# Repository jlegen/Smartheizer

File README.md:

# Smartheizer
## basic heating control

 I wanted some more control for my ancient heating system:
 * enable heating remotely before returning from holidays in winter :-)
 * record activity of heating system and hot water preparation
 * embed into my <a href="https://iobroker.net"> iobroker</a> system

 ##  The hardware in short:

* provides 3 isolated inputs for recording operation times (oil burner, pumps, hot water preparation)
* 3 relays to control heating operations, night setback remotely
* 3 plugs for DS18B20 temperature sensors
* socket for Wemos D1 Mini (or Pro)
* runs with <a href="https://tasmota.github.io/docs/"> Tasmota</a>

## Software needed
* Tasmota for the Wemos D1 on the PCB, which handles the GPIO inputs, Relays and temperature sensors
* a MQTT broker running somewhere, or a smart home software like iobroker or home assistant with MQTT enabled

## Tasmota config

Wemos D1 configuration in Tasmota:

Some Tasmota configurations can be easily applied using the web console. 

1) The GPIO polarity needs to be fixed:
<pre>
Backlog Switchmode1 2; Switchmode2 2; Switchmode3 2
</pre>

2) You also need to decouple the "Switches" (which are the GPIO inputs) from the Relays (it seems like a sort of 'tradition' with tasmota, that per default "Switch1" always triggers "Relay1" etc.).
<pre>
Rule1 on Switch1#state do Publish tele/tasmota_6E171C/SENSOR {"Time":"%timestamp%", "Burner":"%value%"} endon on Switch2#state do Publish tele/tasmota_6E171C/SENSOR {"Time":"%timestamp%", "Pump1":"%value%"} endon on Switch3#state do Publish tele/tasmota_6E171C/SENSOR {"Time":"%timestamp%", "Pump2":"%value%"} endon

Rule1 1
</pre>

Of course, you may chose different topics for MQTT. 
Btw, you don't even need to use these topics with your iobroker or other software - defining the "Rule1" alone enables Tasmota to send the switch states with MQTT as well.

New PCB revision

It works! :-)

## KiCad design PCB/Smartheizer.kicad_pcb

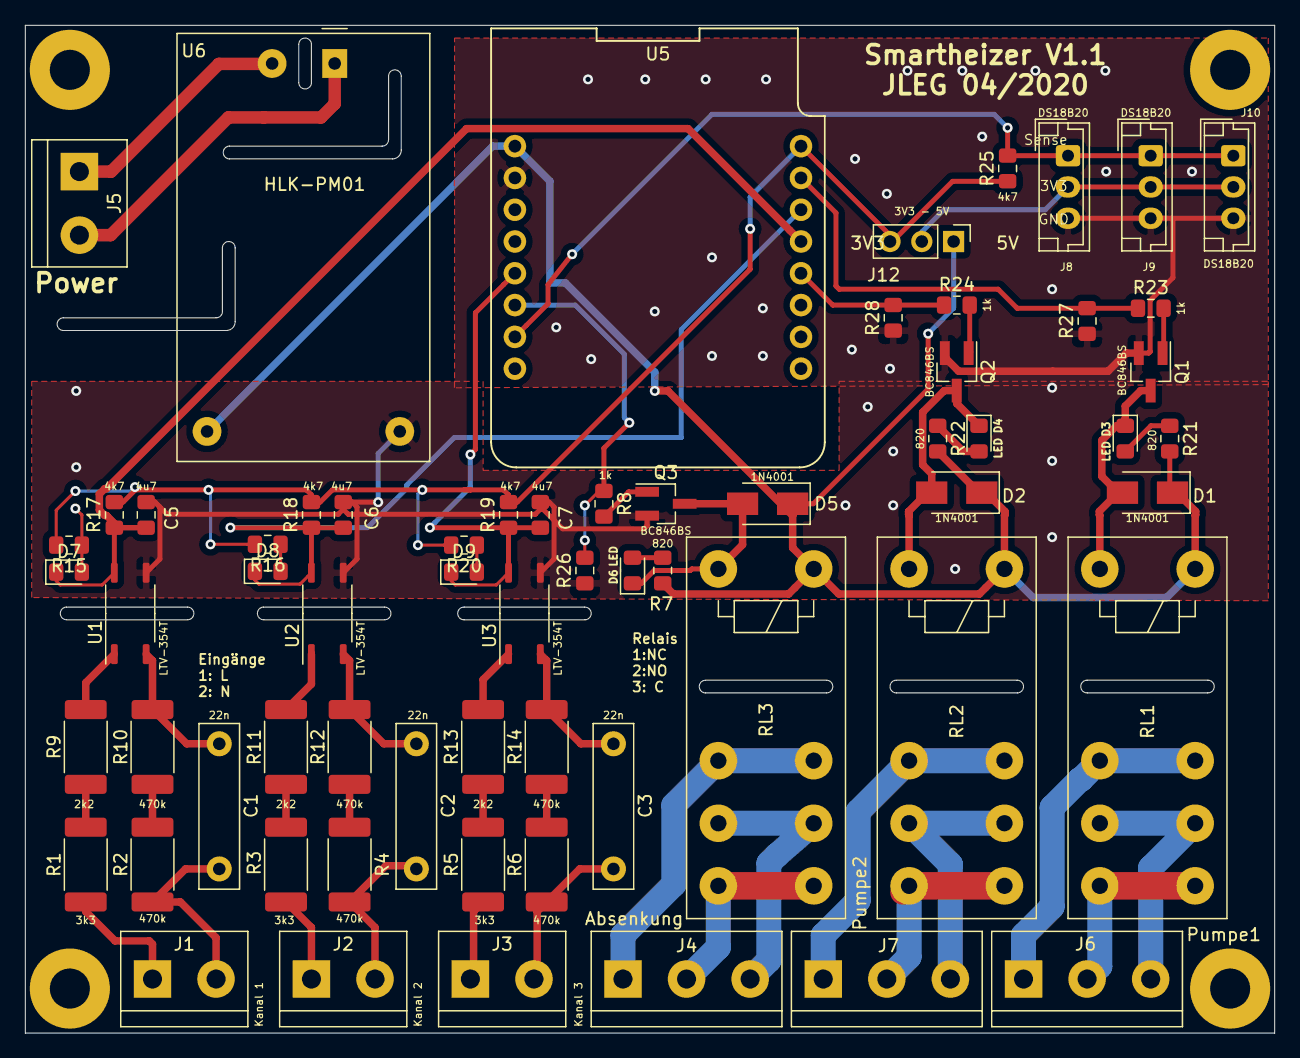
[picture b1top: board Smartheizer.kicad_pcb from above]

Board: 2 copper layers, 99.8 x 80.5 mm, 69 parts (0 on the bottom side), 52 nets.

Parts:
C1, C2, C3: 22n; C_Rect_L13.0mm_W3.0mm_P10.00mm_FKS3_FKP3_MKS4
C5, C6, C7: 4u7; C_0805_2012Metric_Pad1.15x1.40mm_HandSolder
D1, D2, D5: 1N4001; D_SMA
D3, D4, D6, D7, D8, D9: LED; LED_0805_2012Metric_Pad1.15x1.40mm_HandSolder
H1, H2, H3, H4: MountingHole; MountingHole_3.2mm_M3_Pad
J1, J2, J3, J5: Screw_Terminal_01x02; TerminalBlock_bornier-2_P5.08mm
J4: Absenkung; TerminalBlock_bornier-3_P5.08mm
J6: Pumpe1; TerminalBlock_bornier-3_P5.08mm
J7: Pumpe2; TerminalBlock_bornier-3_P5.08mm
J8, J9, J10: DS18B20; JST_EH_B03B-EH-A_1x03_P2.50mm_Vertical
J12: 3V3 - 5V; PinHeader_1x03_P2.54mm_Vertical
Q1, Q2, Q3: BC846BS; SOT-23_Handsoldering
R1, R3, R5: 3k3; R_2512_6332Metric_Pad1.52x3.35mm_HandSolder
R2, R4, R6, R10, R12, R14: 470k; R_2512_6332Metric_Pad1.52x3.35mm_HandSolder
R7, R21, R22: 820; R_0805_2012Metric_Pad1.15x1.40mm_HandSolder
R8, R15, R16, R20, R23, R24: 1k; R_0805_2012Metric_Pad1.15x1.40mm_HandSolder
R9, R11, R13: 2k2; R_2512_6332Metric_Pad1.52x3.35mm_HandSolder
R17, R18, R19, R25: 4k7; R_0805_2012Metric_Pad1.15x1.40mm_HandSolder
R26, R27, R28: 10k; R_0805_2012Metric_Pad1.15x1.40mm_HandSolder
RL1, RL2, RL3: G5Q-1; Relay_SPDT_Schrack-RP-II-1-16A-FormC_RM5mm
U1, U2, U3: LTV-354T; SOIC-4_4.55x3.7mm_P2.54mm
U5: WeMos_mini; wemos-d1-mini-with-pin-header-and-connector
U6: HLK-PM01; Converter_ACDC_HiLink_HLK-PMxx

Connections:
+5V: D1.1, D2.1, D5.1, J12.1, R7.2, R21.2, R22.2, RL1.A1, RL2.A1, RL3.A1, U5.1, U6.4
GND: C5.2, C6.2, C7.2, J8.3, J9.3, J10.3, Q1.2, Q2.2, Q3.2, R26.1, R27.1, R28.1, U1.4, U2.4, U3.4, U5.2, U6.3
unnamed: C1.1, R10.1, U1.3
unnamed: C1.2, J1.2, R2.2
unnamed: C2.1, R12.1, U2.3
unnamed: C2.2, J2.2, R4.2
unnamed: C3.1, R14.1, U3.3
unnamed: C3.2, J3.2, R6.2
unnamed: C5.1, D7.1, R17.1, U1.6, U5.13
unnamed: C6.1, D8.1, R18.1, U2.6, U5.14
unnamed: C7.1, D9.1, R19.1, U3.6, U5.5
unnamed: D1.2, D3.1, Q1.3, RL1.A2
unnamed: D2.2, D4.1, Q2.3, RL2.A2
unnamed: D3.2, R21.1
unnamed: D4.2, R22.1
unnamed: D5.2, D6.1, Q3.3, RL3.A2
unnamed: D6.2, R7.1
unnamed: D7.2, R15.1
unnamed: D8.2, R16.1
unnamed: D9.2, R20.1
unnamed: J1.1, R1.2
unnamed: J2.1, R3.2
unnamed: J3.1, R5.2
unnamed: J4.1, RL3.12
unnamed: J4.2, RL3.14
unnamed: J4.3, RL3.11
unnamed: J5.1, U6.2
unnamed: J5.2, U6.1
unnamed: J6.1, RL1.12
unnamed: J6.2, RL1.14
unnamed: J6.3, RL1.11
unnamed: J7.1, RL2.12
unnamed: J7.2, RL2.14
unnamed: J7.3, RL2.11
unnamed: J8.1, J9.1, J10.1, R25.2, U5.7
unnamed: J8.2, J9.2, J10.2, J12.2
unnamed: J12.3, R15.2, R16.2, R17.2, R18.2, R19.2, R20.2, R25.1, U5.16
unnamed: Q1.1, R23.2
unnamed: Q2.1, R24.2
unnamed: Q3.1, R8.2
unnamed: R1.1, R9.2
unnamed: R9.1, U1.1
unnamed: R2.1, R10.2
unnamed: R11.1, U2.1
unnamed: R3.1, R11.2
unnamed: R4.1, R12.2
unnamed: R13.1, U3.1
unnamed: R5.1, R13.2
unnamed: R6.1, R14.2
unnamed: R23.1, R27.2, U5.15
unnamed: R24.1, R28.2, U5.12
unnamed: R8.1, R26.2, U5.6

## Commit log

2020-08-24 initial upload of PCB
    Kicad files complete
2020-08-26 added image, tasmota config docs
2020-08-26 fix image
2020-08-26 add switchmode config
2020-08-28 Add pcb image
    Populated pcb in action
2020-08-28 Added final pcb
2020-08-29 Update README.md
    Added chart
2021-02-23 added pcb img
    PCB rendered
